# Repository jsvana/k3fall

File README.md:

# k3fall

K3 IF waterfall server: captures the K3's IF output via RSP2pro SDR, streams real-time spectrograms to a web browser, provides console UI for dial tracking and CAT click-to-tune frequency control, all running on a Raspberry Pi 5.

## Quick Start (Dev Mode)

Any machine with Rust installed can run k3fall in dev mode without hardware:

```bash
cargo run
```

Then open http://localhost:8080 in your browser to see the web UI and console.

## Raspberry Pi 5 Setup (One-Time)

### 1. Install SDRplay API v3 (aarch64)

Download the interactive installer from [SDRplay](https://www.sdrplay.com/api/):

```bash
cd ~/Downloads
chmod +x SDRplay_RSP_API-Linux-3.x.x.run
./SDRplay_RSP_API-Linux-3.x.x.run
```

Follow the installer prompts; it will install to `/usr/local/include/` and `/usr/local/lib/`.

### 2. Install SoapySDR and SoapySDRPlay3

On recent Raspberry Pi OS / Debian:

```bash
sudo apt install soapysdr-module-sdrplay3 soapysdr-tools
```

If the package is not available, build from source following SoapySDR documentation.

Verify the driver is installed:

```bash
SoapySDRUtil --probe=driver=sdrplay
```

### 3. Create k3fall User

Add a system user with access to USB devices:

```bash
sudo useradd -r -s /usr/sbin/nologin k3fall
sudo usermod -a -G dialout,plugdev k3fall
```

### 4. Wire Hardware

- **RSP2pro → K3 IF OUT**: Connect RSP2pro USB to Raspberry Pi; wire RSP2pro Tuner 1 SMA to K3's KXV3 IF OUT connector.
- **K3 serial (CAT) → Raspberry Pi**: Connect K3's RS-232 output (via USB-serial adapter) to Raspberry Pi USB.
  - K3 CAT speed: 38400 baud (set in K3 `CONFIG:RS232`).
  - Map the device in `config.toml` (typically `/dev/ttyUSB0` or `/dev/ttyUSB1`).

## Configuration

Copy the example config and edit as needed:

```bash
sudo cp config.example.toml /etc/k3fall/config.toml
sudo nano /etc/k3fall/config.toml
```

Config sections:

- **`[sdr]`**: Driver, center frequency (Hz), sample rate (Hz), gain (dB), antenna port.
  - `driver = "sdrplay"` for RSP2pro; `"file"` for dev-mode tone generation.
  - `center_hz`, `sample_rate`: Set to match your IF strip (e.g., 8215 kHz for K3's 9 MHz IF).
  - `gain_db`: Typical 35–45 dB; adjust for your signal strength.

- **`[cat]`**: K3 CAT interface.
  - `enabled`: Set to `true` on Pi; `false` for dev mode.
  - `device`: Serial port (e.g., `/dev/ttyUSB0`).
  - `baud`: 38400 (K3 default).

- **`[dsp]`**: DSP parameters.
  - `fft_size`: 32768 gives ~8 Hz per bin at 250 kSps; increase for finer resolution.
  - `rows_per_sec`: 30 = one spectrum row every ~33 ms.
  - `ref_level_db`, `range_db`: Set waterfall brightness and contrast; adjust for visibility.

- **`[[bands]]`**: Define amateur bands.
  - `name`, `low_hz`, `high_hz`: Band name and edges.
  - `direction`: `+1` (normal) or `-1` (inverted) depending on K3 injection side. Start with the example; use UI INV chip to verify, then persist the correct value.

- **`[server]`**: Web server listen address and port.

## Build Prerequisites (Pi)

`make deploy` builds on the Pi itself with `--features soapy`, which needs a Rust toolchain and several native dev packages beyond the runtime SoapySDR/SDRplay packages installed above (those provide the *libraries*, not the headers/build tooling `cargo build` needs to link against them).

Install Rust (if not already present):

```bash
curl --proto '=https' --tlsv1.2 -sSf https://sh.rustup.rs | sh
```

Install native build dependencies:

```bash
sudo apt install build-essential pkg-config libudev-dev libclang-dev libsoapysdr-dev
```

- `build-essential`, `pkg-config`: standard toolchain needed by most `-sys` crates.
- `libudev-dev`: required by the `serialport` crate (K3 CAT serial port).
- `libclang-dev`, `libsoapysdr-dev`: required by `soapysdr-sys`'s bindgen step — `libsoapysdr-dev` provides the SoapySDR *headers*, which are not included in the `soapysdr-module-sdrplay3`/`soapysdr-tools` runtime packages installed in step 2 above.

## Deploy to Raspberry Pi

Run from your dev machine with k3fall source and SSH access to the Pi:

```bash
make deploy PI=<pi-hostname-or-ip>
```

The deploying user must have sudo rights on the Pi (with or without password). If using a password, the prompt will appear during deployment. To avoid password prompts, configure passwordless sudo for the deploying user on the Pi (optional).

This will:

1. Rsync source code to `<pi>:~/k3fall-src` (excluding target, .git, .superpowers, mockups).
2. SSH into the Pi and build with `cargo build --release --features soapy`.
3. Install the binary to `/usr/local/bin/k3fall`.
4. Create `/etc/k3fall/` and preserve existing `config.toml`.
5. Install systemd unit and enable/restart the service.

Once deployed, the k3fall service starts automatically on boot and restarts on failure.

## Hardware Verification

After deployment, verify the setup:

- **Waterfall displays band activity**: Open http://pi-address:8080 and confirm signal activity on the waterfall.
- **Dial tracks**: Click in the frequency dial area; the marker should follow your click.
- **Click-to-tune moves K3**: Click a frequency on the waterfall; the K3 should QSY to that frequency.
- **Inversion per band**: Check that spectrum orientation matches your expectation (LSB on left / USB on right). Use the UI INV chip to flip if needed, then update `config.toml` `direction` field.
- **USB recovery**: Disconnect and reconnect the RSP2pro USB and K3 serial; the service should reconnect and resume operation within seconds.

## Development

Build locally:

```bash
cargo build
```

Run tests:

```bash
cargo test
```

Format and lint:

```bash
make quality
```

(or `cargo fmt` and `cargo clippy -- -D warnings` individually)

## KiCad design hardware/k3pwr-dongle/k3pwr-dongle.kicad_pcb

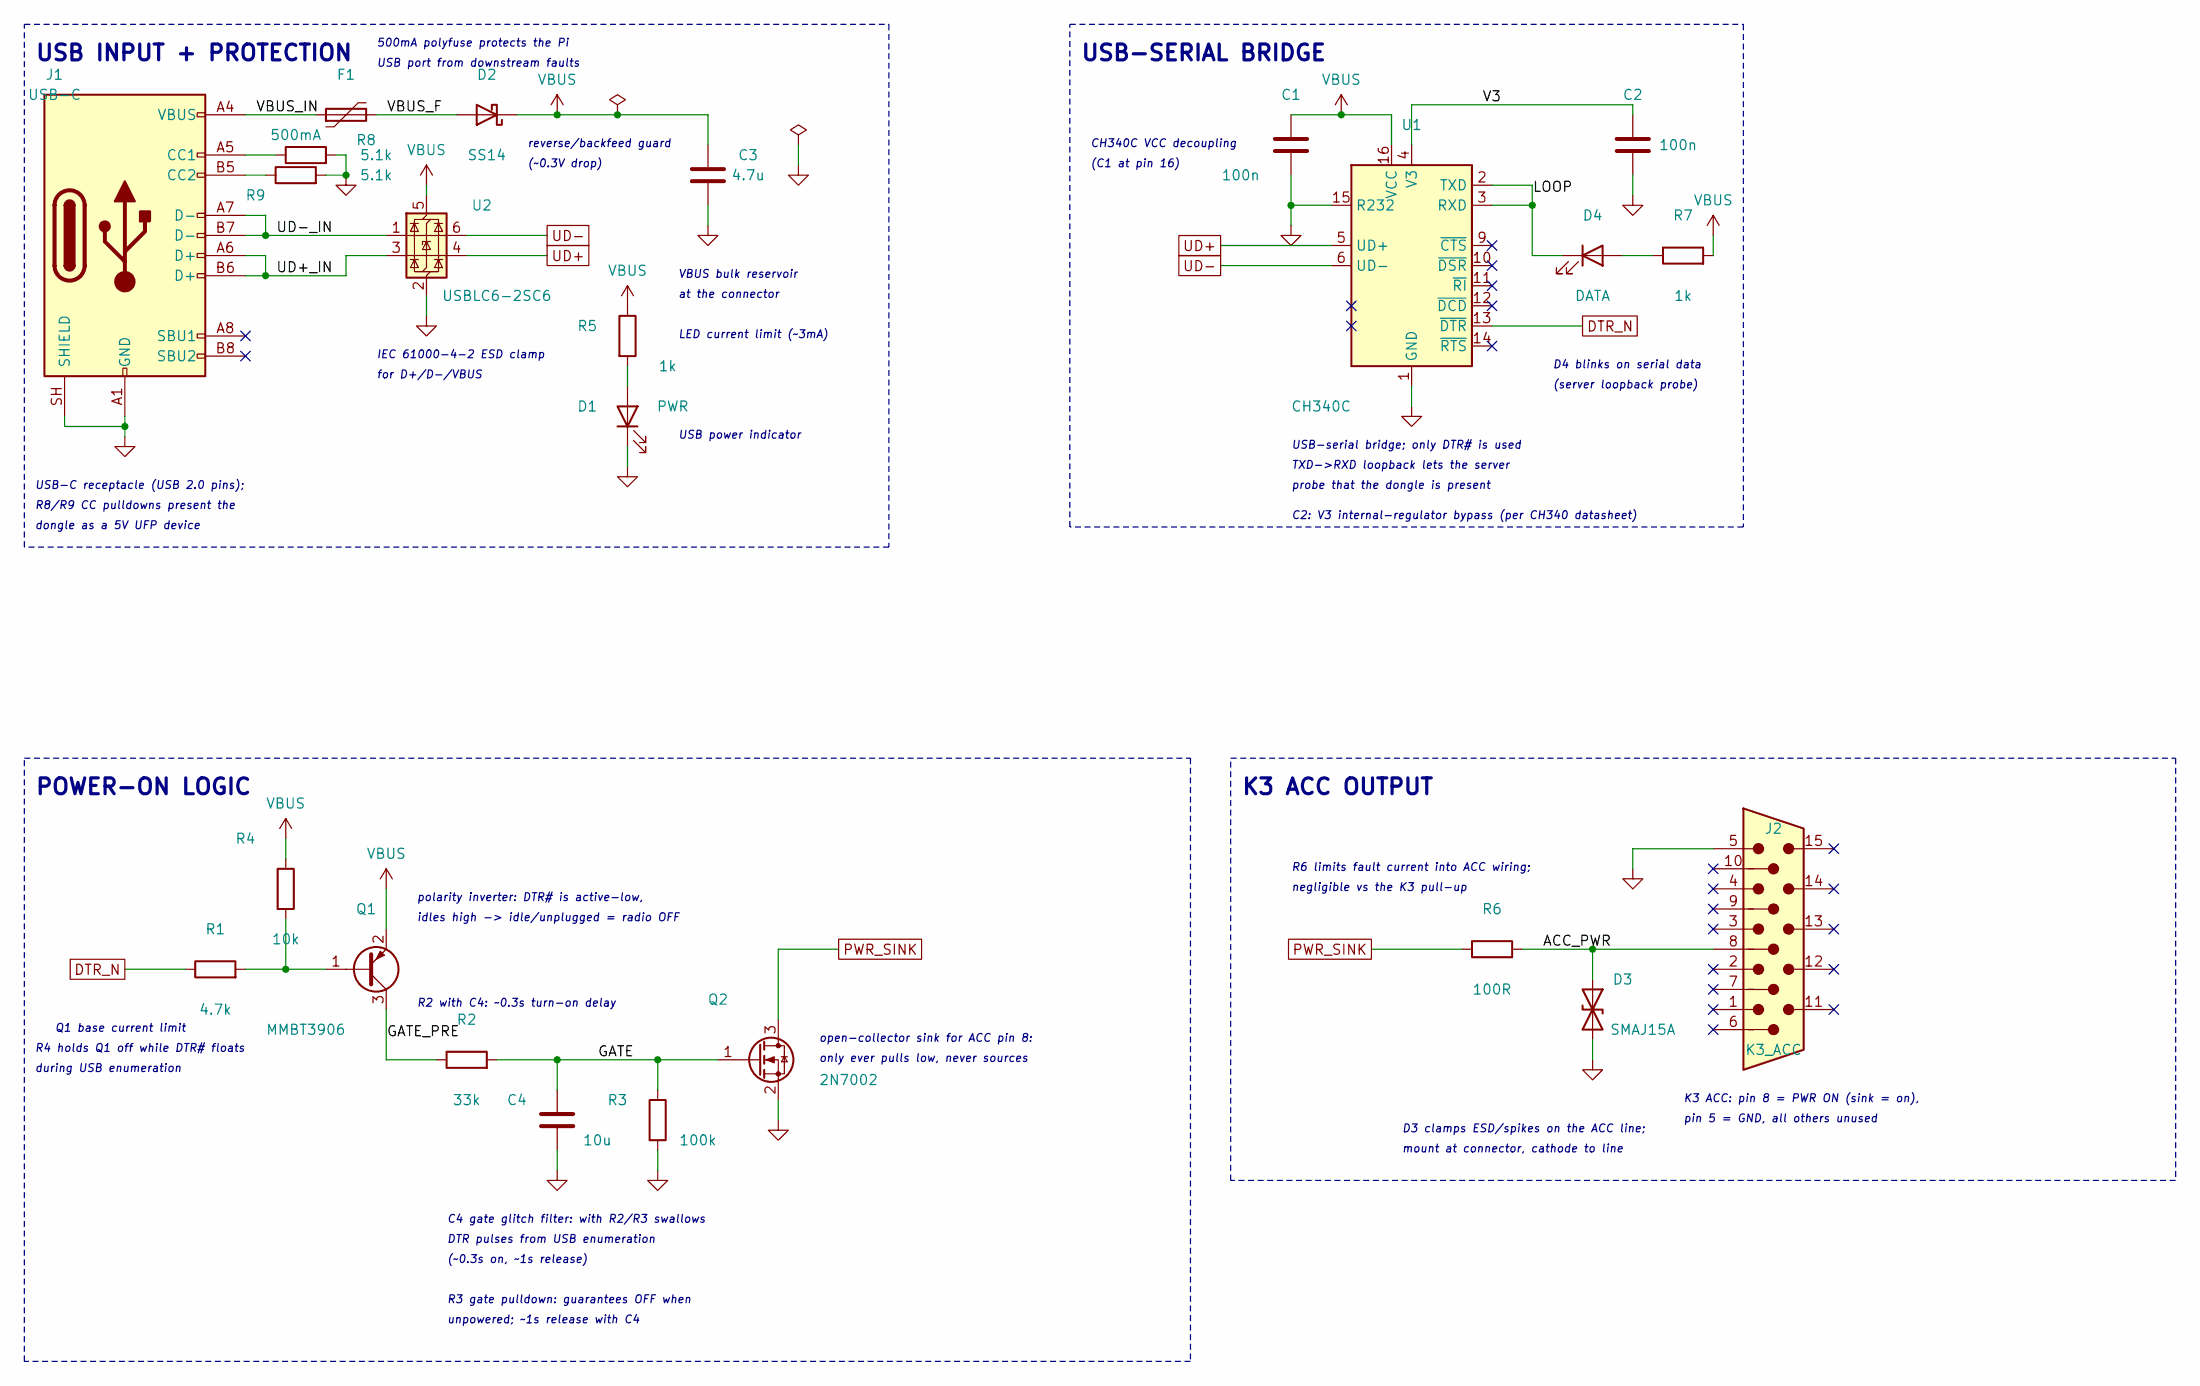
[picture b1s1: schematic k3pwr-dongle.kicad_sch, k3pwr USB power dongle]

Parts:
C1, C2: 100n; C_0603_1608Metric; LCSC C14663
C3: 4.7u; C_0805_2012Metric; LCSC C1779
C4: 10u; C_0805_2012Metric; LCSC C15850
D1: PWR; LED_0805_2012Metric; LCSC C2297
D2: SS14; D_SMA; LCSC C2480
D3: SMAJ15A; D_SMA; LCSC C19077535
D4: DATA; LED_0805_2012Metric; LCSC C2296
F1: 500mA; Fuse_1206_3216Metric; LCSC C720075
J1: USB-C; USB_C_Receptacle_HRO_TYPE-C-31-M-12; LCSC C165948
J2: K3_ACC; DSUB-15-HD_Pins_Horizontal_P2.29x2.54mm_EdgePinOffset8.35mm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
Q1: MMBT3906; SOT-23; LCSC C7420354
Q2: 2N7002; SOT-23; LCSC C916396
R1: 4.7k; R_0603_1608Metric; LCSC C23162
R2: 33k; R_0603_1608Metric; LCSC C4216
R3: 100k; R_0603_1608Metric; LCSC C25803
R4: 10k; R_0603_1608Metric; LCSC C25804
R5, R7: 1k; R_0603_1608Metric; LCSC C21190
R6: 100R; R_0603_1608Metric; LCSC C22775
R8, R9: 5.1k; R_0603_1608Metric; LCSC C23186
U1: CH340C; SOIC-16_3.9x9.9mm_P1.27mm; LCSC C84681
U2: USBLC6-2SC6; SOT-23-6; LCSC C2687116

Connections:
/ACC_PWR: D3.1 (A1), J2.8, R6.2
/GATE: C4.1, Q2.1 (G), R2.2, R3.1
/GATE_PRE: Q1.3 (C), R2.1
/LOOP: D4.1 (K), U1.2 (TXD), U1.3 (RXD)
/UD+_IN: J1.A6 (D+), J1.B6 (D+), U2.3 (I/O2)
/UD-_IN: J1.A7 (D-), J1.B7 (D-), U2.1 (I/O1)
/V3: C2.1, U1.4 (V3)
/VBUS_F: D2.2 (A), F1.2
/VBUS_IN: F1.1, J1.A4 (VBUS), J1.A9 (VBUS), J1.B4 (VBUS), J1.B9 (VBUS)
DTR_N: R1.1, U1.13 (~DTR)
GND: C1.2, C2.2, C3.2, C4.2, D1.1 (K), D3.2 (A2), J1.A1 (GND), J1.A12 (GND), J1.B1 (GND), J1.B12 (GND), J1.SH (SHIELD), J2.5, J2.SH, Q2.2 (S), R3.2, R8.2, R9.2, U1.1 (GND), U1.15 (R232), U2.2 (GND)
unnamed: D1.2 (A), R5.2
unnamed: D4.2 (A), R7.1
unnamed: J1.A5 (CC1), R8.1
unnamed: J1.B5 (CC2), R9.1
unnamed: Q1.1 (B), R1.2, R4.2
PWR_SINK: Q2.3 (D), R6.1
UD+: U1.5 (UD+), U2.4 (I/O2)
UD-: U1.6 (UD-), U2.6 (I/O1)
VBUS: C1.1, C3.1, D2.1 (K), Q1.2 (E), R4.1, R5.1, R7.2, U1.16 (VCC), U2.5 (VBUS)

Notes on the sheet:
USB INPUT + PROTECTION
USB-SERIAL BRIDGE
POWER-ON LOGIC
K3 ACC OUTPUT
USB-C receptacle (USB 2.0 pins);
R8/R9 CC pulldowns present the
dongle as a 5V UFP device
500mA polyfuse protects the Pi
USB port from downstream faults
reverse/backfeed guard
(~0.3V drop)
VBUS bulk reservoir
at the connector
IEC 61000-4-2 ESD clamp
for D+/D-/VBUS
LED current limit (~3mA)
USB power indicator
CH340C VCC decoupling
(C1 at pin 16)
D4 blinks on serial data
(server loopback probe)
USB-serial bridge; only DTR# is used
TXD->RXD loopback lets the server
probe that the dongle is present
C2: V3 internal-regulator bypass (per CH340 datasheet)
Q1 base current limit
R4 holds Q1 off while DTR# floats
during USB enumeration
polarity inverter: DTR# is active-low,
idles high -> idle/unplugged = radio OFF
R2 with C4: ~0.3s turn-on delay
C4 gate glitch filter: with R2/R3 swallows
DTR pulses from USB enumeration
(~0.3s on, ~1s release)
R3 gate pulldown: guarantees OFF when
unpowered; ~1s release with C4
open-collector sink for ACC pin 8:
only ever pulls low, never sources
R6 limits fault current into ACC wiring;
negligible vs the K3 pull-up

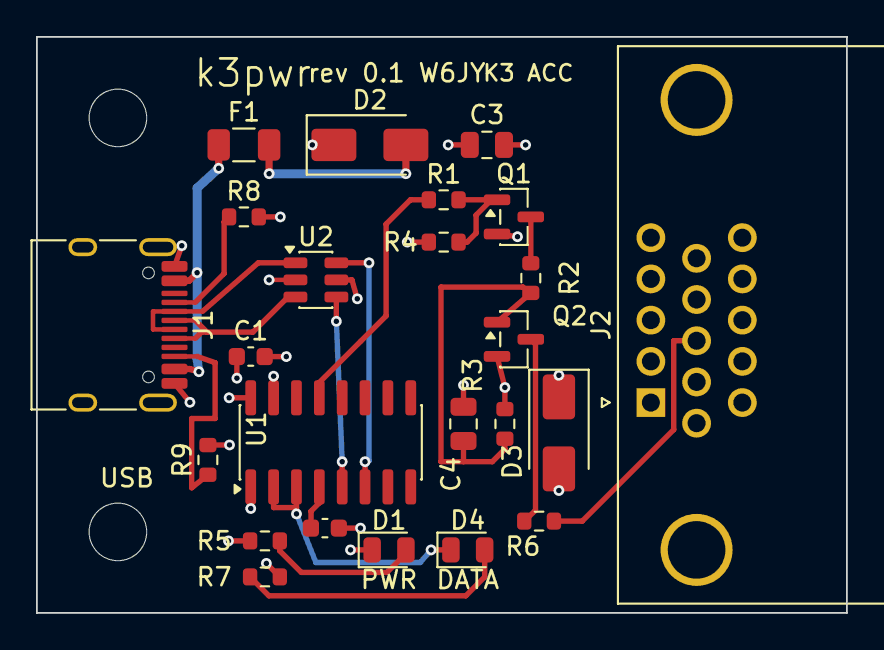
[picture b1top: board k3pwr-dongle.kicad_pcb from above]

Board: 4 copper layers, 45.0 x 32.0 mm, 26 parts (0 on the bottom side), 20 nets.

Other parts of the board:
H1, H2: M3; MountingHole_3.2mm_M3

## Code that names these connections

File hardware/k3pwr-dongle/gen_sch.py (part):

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wired: components connect pin-to-pin within four boxed functional groups
(USB input/protection, USB-serial bridge, power-on logic, K3 ACC output),
GND/VBUS use power symbols, and only the nets that cross groups (VBUS, UD+,
UD-, DTR_N, PWR_SINK) use global labels. NC pins get no_connect markers.
Verify with check_nets.py after regenerating."""
import re, uuid

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wire(P("J1", "A4"), P("F1", "1"))                      # VBUS_IN
for pn in ("A9", "B4", "B9"):
    P("J1", pn)                                        # stacked with A4
LLABELS.append(("VBUS_IN", 41.91, 29.21))
wire(P("F1", "2"), P("D2", "2"))                       # VBUS_F -> anode
LLABELS.append(("VBUS_F", 58.42, 29.21))
wire(P("D2", "1"), (99.06, 29.21), P("C3", "1"))       # cathode = VBUS rail
vbus(80.01, 29.21); JUNCTIONS.append((80.01, 29.21))
flag(1, 87.63, 29.21); JUNCTIONS.append((87.63, 29.21))
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wire(P("U1", "5"), (163.83, 45.72)); GLABELS.append(("UD+", 163.83, 45.72, 180))
wire(P("U1", "6"), (163.83, 48.26)); GLABELS.append(("UD-", 163.83, 48.26, 180))
wire(P("U1", "2"), (203.20, 38.10), (203.20, 40.64), P("U1", "3"))  # loopback
LLABELS.append(("LOOP", 203.20, 39.37))
# Data-activity LED: sinks into TXD (loopback), lights on the server's probe.
wire((203.20, 40.64), (203.20, 46.99), P("D4", "1"))
JUNCTIONS.append((203.20, 40.64))
wire(P("D4", "2"), P("R7", "1"))
wire(P("R7", "2"), (226.06, 44.45)); vbus(226.06, 44.45)
wire(P("U1", "13"), (209.55, 55.88)); GLABELS.append(("DTR_N", 209.55, 55.88, 0))

# --- Group C wiring: DTR# -> inverter -> RC delay -> switch ----------------
GLABELS.append(("DTR_N", 25.40, 137.16, 180))
wire((25.40, 137.16), P("R1", "1"))
wire(P("R1", "2"), P("Q1", "1"))                       # Q1B
wire(P("R4", "2"), (45.72, 137.16)); JUNCTIONS.append((45.72, 137.16))
wire(P("R4", "1"), (45.72, 120.65)); vbus(45.72, 120.65)
wire(P("Q1", "2"), (58.42, 127.00)); vbus(58.42, 127.00)
wire(P("Q1", "3"), (58.42, 148.59), P("R2", "1"))      # GATE_PRE
LLABELS.append(("GATE_PRE", 58.42, 146.05))
wire(P("R2", "2"), P("Q2", "1"))                       # GATE line
LLABELS.append(("GATE", 85.09, 148.59))
wire(P("C4", "1"), (80.01, 148.59)); JUNCTIONS.append((80.01, 148.59))
wire(P("C4", "2"), (80.01, 162.56)); gnd(80.01, 162.56)
wire(P("R3", "1"), (92.71, 148.59)); JUNCTIONS.append((92.71, 148.59))
wire(P("R3", "2"), (92.71, 162.56)); gnd(92.71, 162.56)
wire(P("Q2", "3"), (107.95, 134.62), (115.57, 134.62))
GLABELS.append(("PWR_SINK", 115.57, 134.62, 0))
wire(P("Q2", "2"), (107.95, 156.21)); gnd(107.95, 156.21)

# --- Group D wiring: limiter -> TVS -> DE-15HD -----------------------------
GLABELS.append(("PWR_SINK", 182.88, 134.62, 180))
wire((182.88, 134.62), P("R6", "1"))
wire(P("R6", "2"), P("J2", "8"))                       # ACC_PWR
LLABELS.append(("ACC_PWR", 204.47, 134.62))
wire(P("D3", "1"), (210.82, 134.62)); JUNCTIONS.append((210.82, 134.62))
wire(P("D3", "2"), (210.82, 148.59)); gnd(210.82, 148.59)
wire(P("J2", "5"), (215.90, 121.92), (215.90, 124.46)); gnd(215.90, 124.46)
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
